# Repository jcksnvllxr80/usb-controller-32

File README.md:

# USB Controller 32

A USB HID gamepad controller built on the **PIC32MX250F128B** microcontroller. The firmware reads button inputs from GPIO pins, two potentiometers on the PIC32 ADC, and an **MCP23017** I2C I/O expander, then reports them to a host PC as a standard USB HID gamepad. The board-level serial path uses a **MAX3232** level shifter, and the MCU clock is provided by a **20 MHz crystal**. Built with **MPLAB Harmony 3**, **FreeRTOS**, and **C++**.

## Features

- USB HID gamepad with 18 button inputs (2 direct GPIO + 16 via MCP23017)
- 8-byte HID input report with 18 buttons, hat switch, and two live analog axes
- MCP23017 I2C I/O expander with interrupt-driven input detection
- MAX3232-backed debug serial / RS-232 path
- `POT_1` and `POT_2` sampled on `AN4` / `AN5` for `Z` and `Rz`
- Send-on-change HID reports for buttons and potentiometer axes
- Rate-limited serial logging for potentiometer changes with `POT_1` / `POT_2` identification
- FreeRTOS-based task scheduling
- UART debug logging and USB/HID diagnostics
- Green and red status LEDs

## Hardware Used

Main ICs and timing parts on this design:

- `PIC32MX250F128B` - main microcontroller, USB device controller, ADC, GPIO, I2C, and UART
- `MCP23017` - 16-bit I2C GPIO expander for the additional button inputs
- `MAX3232` - UART level shifter for the board's serial / RS-232 debug path
- `20 MHz crystal` - external clock source for the PIC32MX250F128B
- `2x linear potentiometers` - analog controls for `POT_1` and `POT_2`, mapped to HID `Z` and `Rz`
- `Mini USB breakout` - USB connector breakout for the device port, such as the small Adafruit mini USB breakout the board is using

## Architecture

### UML Class Diagram

### State Machine

## Pin Assignment Table

### PIC32MX250F128B Direct I/O

| Signal | Pin | Port | Direction | Description |
|---|---|---|---|---|
| MCLR | 1 | — | Input | Master clear (active-low reset); 10k pull-up to VDD; PICkit 5 pin 1 (VPP) |
| PGED1 | 2 | RA0 | Programming | ICSP data (PICkit 5 pin 4) |
| PGEC1 | 3 | RA1 | Programming | ICSP clock (PICkit 5 pin 5) |
| GREEN_LED | 4 | RB0 | Output | Green status LED |
| RED_LED | 5 | RB1 | Output | Red status LED |
| POT_1 | 6 | RB2 / AN4 | Input | Analog potentiometer mapped to HID Z axis |
| POT_2 | 7 | RB3 / AN5 | Input | Analog potentiometer mapped to HID Rz axis |
| VSS | 8 | — | Power | Ground |
| OSC1 | 9 | RA2 | Input | 20 MHz crystal input |
| OSC2 | 10 | RA3 | Output | 20 MHz crystal output |
| U1TX | 11 | RB4 | Output | UART1 transmit (debug) |
| U1RX | 12 | RA4 | Input | UART1 receive (debug) |
| VDD | 13 | — | Power | 5V supply |
| INTERRUPT_A | 14 | RB5 | Input | MCP23017 Port A interrupt (active-low) |
| VBUS | 15 | — | Power | USB 5V bus voltage; connected to VCC |
| INTERRUPT_B | 16 | RB7 | Input | MCP23017 Port B interrupt (active-low) |
| SCL1 | 17 | RB8 | Output | I2C1 clock to MCP23017 |
| SDA1 | 18 | RB9 | Bidirectional | I2C1 data to MCP23017 |
| VSS | 19 | — | Power | Ground |
| VCAP | 20 | — | Power | Internal core regulator output; 0.1µF cap to VSS |
| D+ | 21 | — | Bidirectional | USB data plus |
| D− | 22 | — | Bidirectional | USB data minus |
| VUSB3V3 | 23 | — | Power | USB 3.3V supply; decoupling capacitors to GND |
| RB13 | 24 | RB13 | NC | Not connected |
| BUTTON_1 | 25 | RB14 | Input | Direct button input 1 |
| BUTTON_2 | 26 | RB15 | Input | Direct button input 2 |
| AVSS | 27 | — | Power | Analog ground |
| AVDD | 28 | — | Power | 5V analog supply |

### MCP23017 I/O Expander (I2C address 0x20)

| Port | Pins | Direction | Pull-ups | Interrupt | Description |
|---|---|---|---|---|---|
| Port A | GPA0–GPA7 | Input | Enabled | Enabled (interrupt-on-change) | 8 button inputs |
| Port B | GPB0–GPB7 | Input | Enabled | Enabled (interrupt-on-change) | 8 button inputs |

### Input/Output Summary

| Type | Count | Source | Details |
|---|---|---|---|
| Button inputs (direct) | 2 | PIC32 GPIO | RB14, RB15 |
| Button inputs (expanded) | 16 | MCP23017 Port A & B | GPA0–7, GPB0–7 |
| Analog inputs | 2 | PIC32 ADC | POT_1 on AN4 drives HID Z, POT_2 on AN5 drives HID Rz |
| LED outputs | 2 | PIC32 GPIO | Green (RB0), Red (RB1) |
| USB HID | 1 | USB peripheral | 18 buttons, hat switch, X/Y centered, live Z/Rz in an 8-byte report |
| Debug UART | 1 | UART1 via MAX3232 | 115200 baud debug/serial path (TX: RB4, RX: RA4) |
| I2C bus | 1 | I2C1 | MCP23017 at 0x20 |

## Getting Started

### Prerequisites

- [MPLAB X IDE](https://www.microchip.com/mplab/mplab-x-ide) or the **MPLAB Extension for VS Code**
- [XC32 Compiler](https://www.microchip.com/xc32) (v4.x or later)
- [PIC32MX DFP](https://packs.download.microchip.com/) v1.6.369
- **PICkit 5** (or compatible Microchip programmer/debugger)
- Git

### Install MPLAB for VS Code

1. Open **VS Code** (or VS Code Insiders).
2. Go to the **Extensions** view (`Ctrl+Shift+X`).
3. Search for **"MPLAB"** and install the **Microchip MPLAB** extension pack.
4. The extension will prompt you to install the **XC32 compiler** and required device packs if they are not found. Follow the prompts.
5. Restart VS Code after installation.

### Clone and Build

```bash
git clone https://github.com/jcksnvllxr80/usb-controller-32.git
cd usb-controller-32
```

1. Open the folder in VS Code.
2. The MPLAB extension should detect the project automatically via the CMake configuration in the `cmake/` directory.
3. Select the **usb-controller-32** project and the **default** configuration from the MPLAB project view.
4. Click **Build** (or press `Ctrl+Shift+B`).

### Program the Device

1. Connect the **PICkit 5** to the ICSP header on your board (ensure correct pin 1 orientation).
2. In the MPLAB extension, select **PICkit 5** as the hardware tool.
3. Set the programming speed to **Low** if you encounter connection issues.
4. Click **Program** to flash the `.hex` file to the PIC32MX250F128B.

> Warning: Use a native **USB 2.0** port when connecting this controller to the PC. On some machines, USB 3.x ports/controllers can fail enumeration or produce a Windows Code 10 error with this hardware. If your machine does not have a USB 2.0 port, connect the controller through a **USB 2.0 hub**.

### Verify Operation

1. After programming, the device should enumerate as a USB HID gamepad on the host PC.
2. Open **Set up USB game controllers** (Windows) or a gamepad tester to confirm button presses and `Z` / `Rz` potentiometer movement are registered.
3. Connect a serial terminal (115200 baud, 8N1) to UART1 to view debug logs, potentiometer change logs, and issue commands.

## UART Diagnostics

Helper scripts:

- `powershell -ExecutionPolicy Bypass -File .\tools\uart_query.ps1`
- `powershell -ExecutionPolicy Bypass -File .\tools\uart_cmd.ps1 -cmd "status"`

Useful commands:

- `status` - GPIO, USB, and LED summary
- `usb` - USB device state and register dump
- `enum` - enumeration counters and last setup request
- `hid` - HID readiness, send counters, and current report bytes
- `usblog` - recent USB transaction log
- `usbdbg` - toggle live USB debug logging
- `usbreset` - soft detach/reattach to force re-enumeration

Automatic serial logs:

- Potentiometer changes are logged automatically as `[POT] POT_1 axis=...` and/or `[POT] POT_2 axis=...`
- Logs are only emitted when the scaled axis value changes
- Pot logs are rate-limited to 5 lines per second total

## Firmware Notes

- GPIO and MCP23017 interrupts only latch state. HID reports are built and sent from `APP_Tasks()`.
- `POT_1` and `POT_2` are polled in `APP_Tasks()`, scaled from 10-bit ADC samples to 8-bit HID axis values, and mapped to HID `Z` and `Rz`.
- Potentiometer state is cached, so a new HID report is only queued when a button changes or when the last-sent `Z` / `Rz` byte changes.
- Potentiometer serial logs identify which input changed (`POT_1`, `POT_2`, or both), skip repeated values, and are rate-limited to 5 lines per second.
- HID reports are only queued when button or axis state changes, which keeps traffic and debug noise down.

## Project Structure

```
usb-controller-32/
├── cmake/                      # CMake build configurations
├── docs/                       # Datasheets, block diagram, images
├── tools/                      # Flash and UART helper scripts
├── usb-controller-32/
│   ├── mcc/                    # MPLAB Code Configurator files
│   └── src/
│       ├── main.cpp            # Entry point (SYS_Initialize + SYS_Tasks)
│       ├── app.cpp / app.h     # App task, GPIO/MCP state, USB HID send path
│       ├── command_handler.cpp / .h # UART command parser and diagnostics
│       ├── gamepad.cpp / .h    # USB HID gamepad driver
│       ├── mcp23017.cpp / .h   # MCP23017 I2C I/O expander driver
│       ├── logger.cpp / .h     # UART debug logger (singleton)
│       ├── usb_debug.c / .h    # USB debug logging helpers
│       ├── config/             # Harmony-generated peripheral config
│       └── third_party/rtos/   # FreeRTOS source
└── README.md
```

## Sponsor

PCB prototyping for this project is sponsored by [PCBWay](https://www.pcbway.com/).

PCBWay makes it easy to go from design files to manufactured boards. Upload your Gerber files, pick your board specs (layers, thickness, surface finish, color, etc.), and get an instant quote. Orders typically ship within a few days. Their online ordering process is straightforward — just create an account, upload your files, review the specs, and check out.

## License

See Microchip's license terms in the source file headers.

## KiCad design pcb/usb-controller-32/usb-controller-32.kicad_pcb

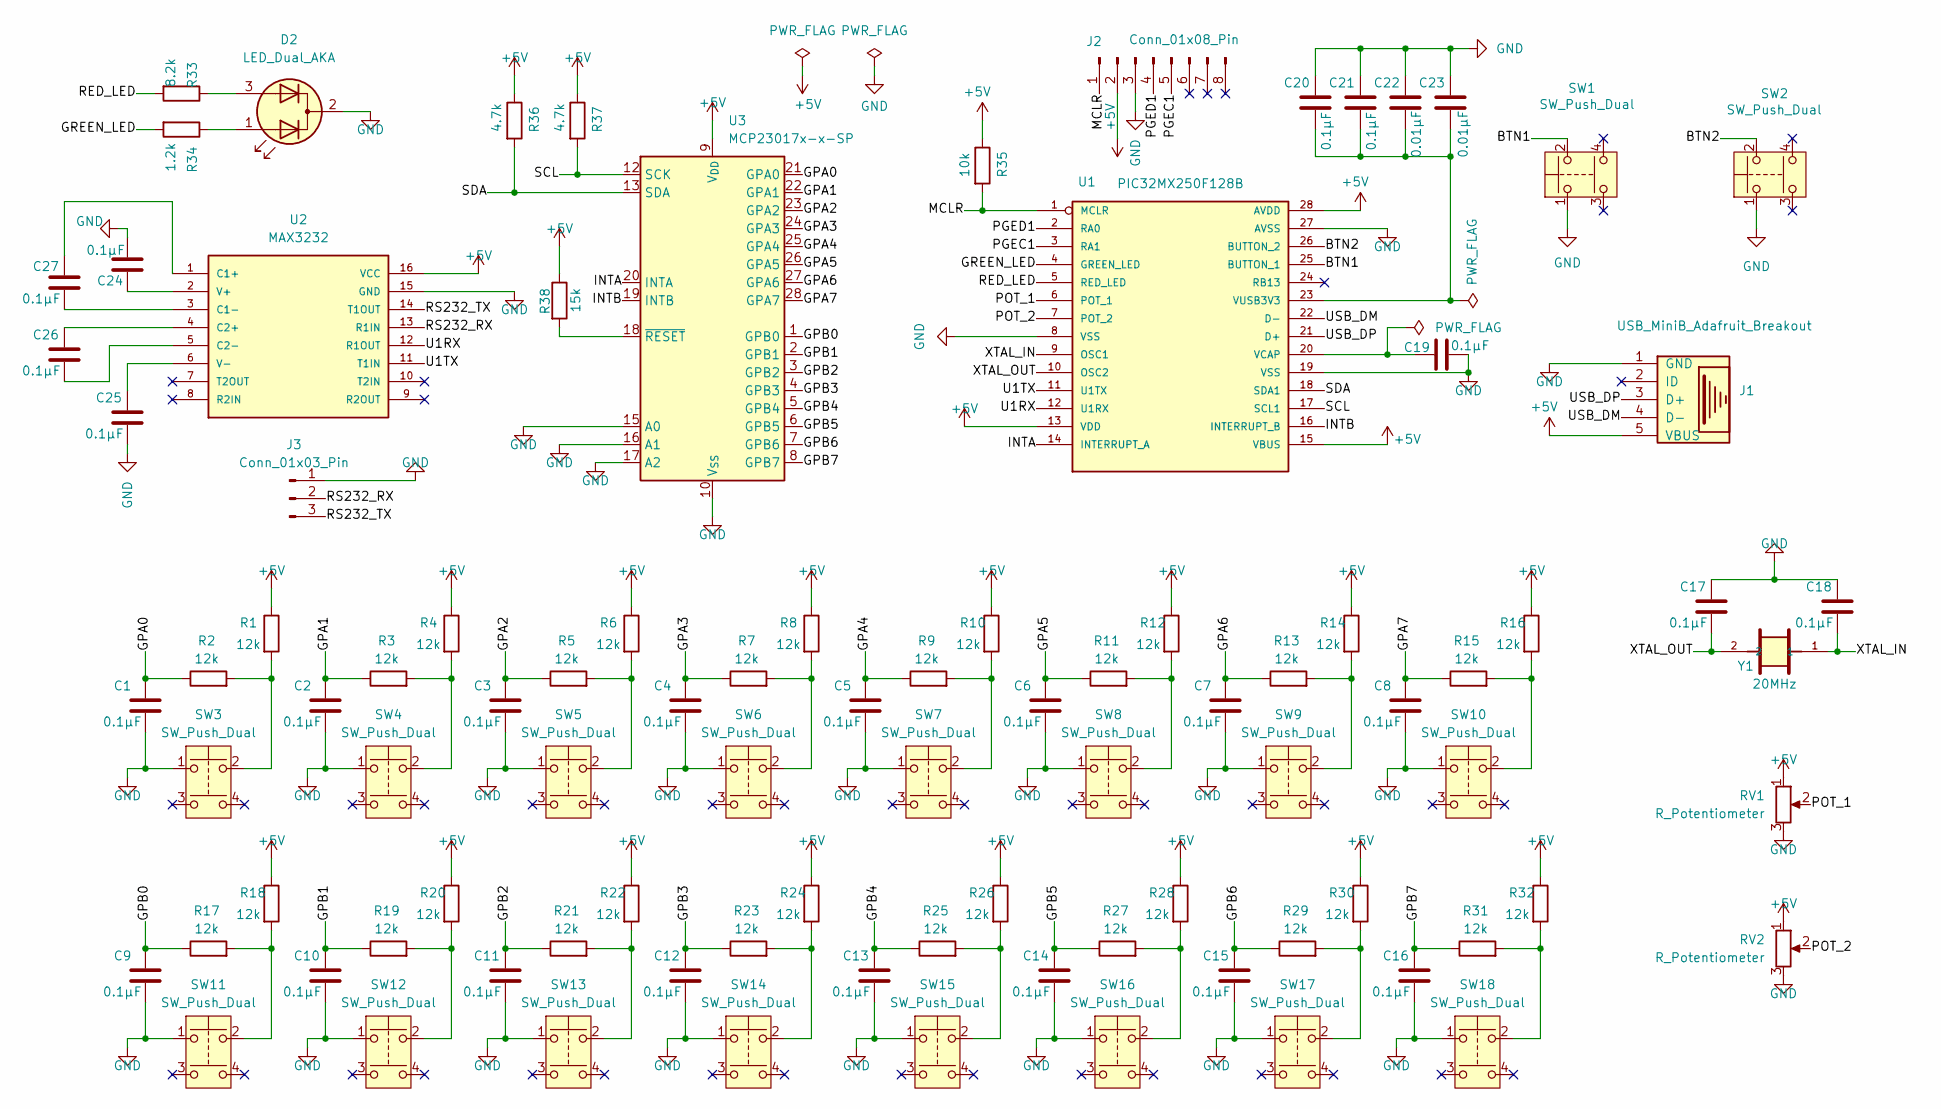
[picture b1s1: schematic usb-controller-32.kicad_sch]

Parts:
C1, C2, C3, C4, C5, C6, C7, C8, C9, C10, C11, C12, C13, C14, C15, C16, C17, C18, C19, C20, C21, C24, C25, C26, C27: 0.1µF; C_Disc_D5.0mm_W2.5mm_P2.50mm
C22, C23: 0.01µF; C_Disc_D5.0mm_W2.5mm_P2.50mm
D2: LED_Dual_AKA; LED_D3.0mm-3
J1: USB_MiniB_Adafruit_Breakout
J2: Conn_01x08_Pin; PinHeader_1x08_P2.54mm_Vertical
J3: Conn_01x03_Pin; PinHeader_1x03_P2.54mm_Vertical
R1, R2, R3, R4, R5, R6, R7, R8, R9, R10, R11, R12, R13, R14, R15, R16, R17, R18, R19, R20, R21, R22, R23, R24, R25, R26, R27, R28, R29, R30, R31, R32: 12k; R_Axial_DIN0207_L6.3mm_D2.5mm_P10.16mm_Horizontal
R33: 8.2k; R_Axial_DIN0207_L6.3mm_D2.5mm_P10.16mm_Horizontal
R34: 1.2k; R_Axial_DIN0207_L6.3mm_D2.5mm_P10.16mm_Horizontal
R35: 10k; R_Axial_DIN0207_L6.3mm_D2.5mm_P10.16mm_Horizontal
R36, R37: 4.7k; R_Axial_DIN0207_L6.3mm_D2.5mm_P10.16mm_Horizontal
R38: 15k; R_Axial_DIN0207_L6.3mm_D2.5mm_P10.16mm_Horizontal
RV1, RV2: R_Potentiometer; Potentiometer_Bourns_3386P_Vertical
SW1, SW2, SW3, SW4, SW5, SW6, SW7, SW8, SW9, SW10, SW11, SW12, SW13, SW14, SW15, SW16, SW17, SW18: SW_Push_Dual; SW_TH_Tactile_Omron_B3F-100x
U1: PIC32MX250F128B; DIP-28_W7.62mm
U2: MAX3232; DIP-16_W7.62mm
U3: MCP23017x-x-SP; DIP-28_W7.62mm
Y1: 20MHz; Crystal_HC49-4H_Vertical

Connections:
+5V: J1.5 (VBUS), J2.2, R1.1, R4.1, R6.1, R8.1, R10.1, R12.1, R14.1, R16.1, R18.1, R20.1, R22.1, R24.1, R26.1, R28.1, R30.1, R32.1, R35.1, R36.1, R37.1, R38.1, RV1.1, RV2.1, U1.13 (VDD), U1.15 (VBUS), U1.28 (AVDD), U2.16 (VCC), U3.9 (V_{DD})
/BTN1: SW1.2, U1.25 (BUTTON_1)
/BTN2: SW2.2, U1.26 (BUTTON_2)
/GPA0: C1.2, R2.1, U3.21 (GPA0)
/GPA1: C2.2, R3.1, U3.22 (GPA1)
/GPA2: C3.2, R5.1, U3.23 (GPA2)
/GPA3: C4.2, R7.1, U3.24 (GPA3)
/GPA4: C5.2, R9.1, U3.25 (GPA4)
/GPA5: C6.2, R11.1, U3.26 (GPA5)
/GPA6: C7.2, R13.1, U3.27 (GPA6)
/GPA7: C8.2, R15.1, U3.28 (GPA7)
/GPB0: C9.2, R17.1, U3.1 (GPB0)
/GPB1: C10.2, R19.1, U3.2 (GPB1)
/GPB2: C11.2, R21.1, U3.3 (GPB2)
/GPB3: C12.2, R23.1, U3.4 (GPB3)
/GPB4: C13.2, R25.1, U3.5 (GPB4)
/GPB5: C14.2, R27.1, U3.6 (GPB5)
/GPB6: C15.2, R29.1, U3.7 (GPB6)
/GPB7: C16.2, R31.1, U3.8 (GPB7)
/GREEN_LED: R34.2, U1.4 (GREEN_LED)
/INTA: U1.14 (INTERRUPT_A), U3.20 (INTA)
/INTB: U1.16 (INTERRUPT_B), U3.19 (INTB)
/MCLR: J2.1, R35.2, U1.1 (MCLR)
/PGEC1: J2.5, U1.3 (RA1)
/PGED1: J2.4, U1.2 (RA0)
/POT_1: RV1.2, U1.6 (POT_1)
/POT_2: RV2.2, U1.7 (POT_2)
/RED_LED: R33.2, U1.5 (RED_LED)
/RS232_RX: J3.2, U2.13 (R1IN)
/RS232_TX: J3.3, U2.14 (T1OUT)
/SCL: R37.2, U1.17 (SCL1), U3.12 (SCK)
/SDA: R36.2, U1.18 (SDA1), U3.13 (SDA)
/U1RX: U1.12 (U1RX), U2.12 (R1OUT)
/U1TX: U1.11 (U1TX), U2.11 (T1IN)
/USB_DM: J1.4 (D-), U1.22 (D-)
/USB_DP: J1.3 (D+), U1.21 (D+)
/XTAL_IN: C18.1, U1.9 (OSC1), Y1.1
/XTAL_OUT: C17.1, U1.10 (OSC2), Y1.2
GND: C1.1, C2.1, C3.1, C4.1, C5.1, C6.1, C7.1, C8.1, C9.1, C10.1, C11.1, C12.1, C13.1, C14.1, C15.1, C16.1, C17.2, C18.2, C19.1, C20.2, C21.2, C22.2, C23.2, C24.1, C25.1, D2.2 (K), J1.1 (GND), J2.3, J3.1, RV1.3, RV2.3, SW1.1, SW2.1, SW3.1, SW4.1, SW5.1, SW6.1, SW7.1, SW8.1, SW9.1, SW10.1, SW11.1, SW12.1, SW13.1, SW14.1, SW15.1, SW16.1, SW17.1, SW18.1, U1.8 (VSS), U1.19 (VSS), U1.27 (AVSS), U2.15 (GND), U3.10 (V_{SS}), U3.15 (A0), U3.16 (A1), U3.17 (A2)
unnamed: D2.1 (A1), R34.1
unnamed: D2.3 (A2), R33.1
unnamed: R1.2, R2.2, SW3.2
unnamed: R3.2, R4.2, SW4.2
unnamed: R5.2, R6.2, SW5.2
unnamed: R7.2, R8.2, SW6.2
unnamed: R9.2, R10.2, SW7.2
unnamed: R11.2, R12.2, SW8.2
unnamed: R13.2, R14.2, SW9.2
unnamed: R15.2, R16.2, SW10.2
unnamed: R17.2, R18.2, SW11.2
unnamed: R19.2, R20.2, SW12.2
unnamed: R21.2, R22.2, SW13.2
unnamed: R23.2, R24.2, SW14.2
unnamed: R25.2, R26.2, SW15.2
unnamed: R27.2, R28.2, SW16.2
unnamed: R29.2, R30.2, SW17.2
unnamed: R31.2, R32.2, SW18.2
unnamed: C19.2, U1.20 (VCAP)
unnamed: C20.1, C21.1, C22.1, C23.1, U1.23 (VUSB3V3)
unnamed: C27.2, U2.1 (C1+)
unnamed: C27.1, U2.3 (C1-)
unnamed: C26.2, U2.4 (C2+)
unnamed: C26.1, U2.5 (C2-)
unnamed: C24.2, U2.2 (V+)
unnamed: C25.2, U2.6 (V-)
unnamed: R38.2, U3.18 (~RESET)

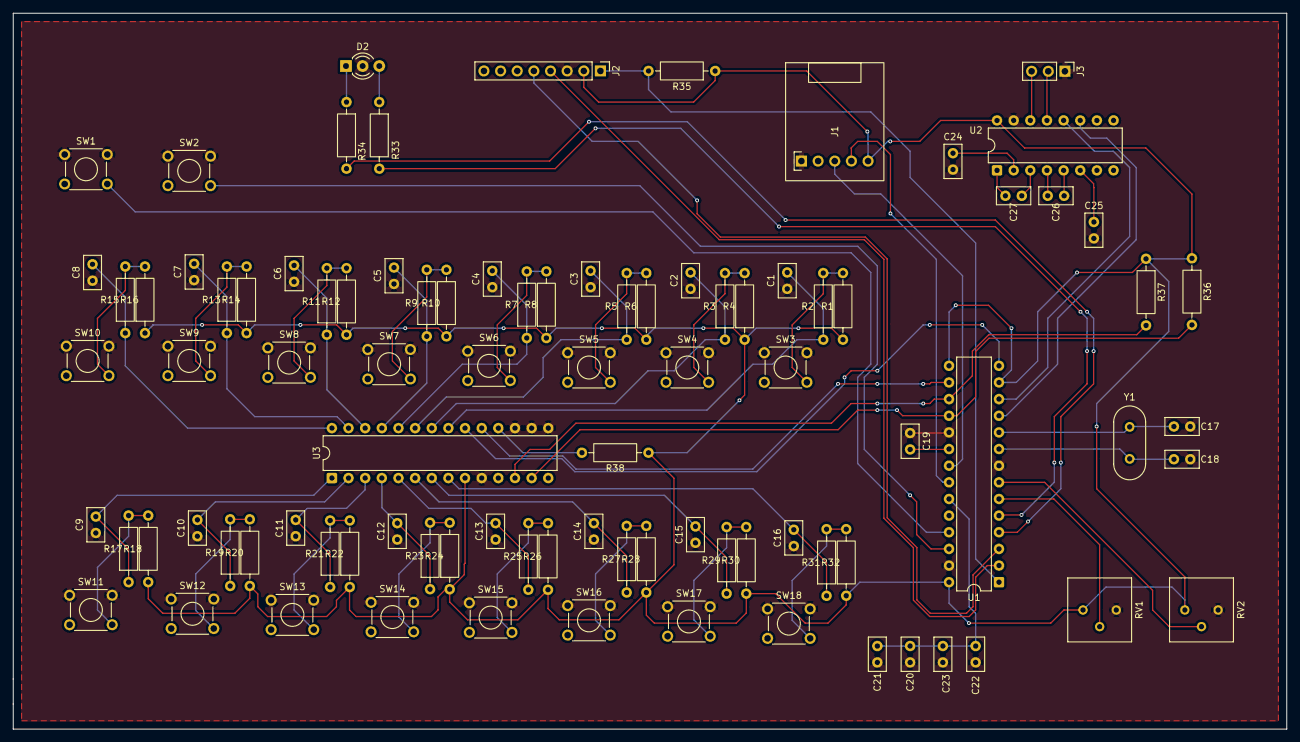
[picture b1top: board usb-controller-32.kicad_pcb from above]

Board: 2 copper layers, 194.3 x 109.2 mm, 93 parts (0 on the bottom side), 66 nets.

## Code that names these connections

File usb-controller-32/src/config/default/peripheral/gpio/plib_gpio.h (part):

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// *****************************************************************************


/*** Macros for GREEN_LED pin ***/
#define GREEN_LED_Set()               (LATBSET = (1<<0))
#define GREEN_LED_Clear()             (LATBCLR = (1<<0))
#define GREEN_LED_Toggle()            (LATBINV= (1<<0))
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#define GREEN_LED_InputEnable()       (TRISBSET = (1<<0))
#define GREEN_LED_Get()               ((PORTB >> 0) & 0x1)
#define GREEN_LED_GetLatch()          ((LATB >> 0) & 0x1)
#define GREEN_LED_PIN                  GPIO_PIN_RB0

/*** Macros for RED_LED pin ***/
#define RED_LED_Set()               (LATBSET = (1<<1))
#define RED_LED_Clear()             (LATBCLR = (1<<1))
#define RED_LED_Toggle()            (LATBINV= (1<<1))
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#define RED_LED_InputEnable()       (TRISBSET = (1<<1))
#define RED_LED_Get()               ((PORTB >> 1) & 0x1)
#define RED_LED_GetLatch()          ((LATB >> 1) & 0x1)
#define RED_LED_PIN                  GPIO_PIN_RB1

/*** Macros for POT_1 pin ***/
#define POT_1_Get()               ((PORTB >> 2) & 0x1)
#define POT_1_GetLatch()          ((LATB >> 2) & 0x1)
#define POT_1_PIN                  GPIO_PIN_RB2

/*** Macros for POT_2 pin ***/
#define POT_2_Get()               ((PORTB >> 3) & 0x1)
#define POT_2_GetLatch()          ((LATB >> 3) & 0x1)
#define POT_2_PIN                  GPIO_PIN_RB3

/*** Macros for INTERRUPT_A pin ***/
#define INTERRUPT_A_Set()               (LATBSET = (1<<5))
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
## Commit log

2026-03-17 Add configuration settings and update component positions in YAML files
2026-03-17 Add FreeRTOS include directories and update heap size configuration
2026-03-17 Update GPIO macros and add BUTTON_1, BUTTON_2, INTERRUPT_A, and INTERRUPT_B definitions
2026-03-17 Implement gamepad functionality with MCP23017 support and logging capabilities
2026-03-17 add docs and images
2026-03-17 add more docs and and put on README
2026-03-17 remove default profile
2026-03-17 Add CHANGE_NOTICE interrupt handling and GPIO callback support
2026-03-17 Implement GPIO interrupt handling and update button state management
2026-03-17 Fix button press detection logic and add logging for button state changes and MCP23017 interrupts
2026-03-22 move clock source from frc to primary osc
2026-03-22 change the i2c brg to 400khz from 50khz
2026-03-22 change chip package in mcc
2026-03-22 remove everything except uart and buttons
2026-03-22 Refactor button handling logic to use interrupt callbacks and improve state tracking
2026-03-22 Add pull-up resistors for PORTB and update button logging
2026-03-22 Fix UART write handling in Logger to ensure txDone_ is set correctly on failure
2026-03-22 add i2c1
2026-03-22 mcp23017 works properly
2026-04-06 add max3232cpe datasheet
2026-04-06 Update USB Controller configuration and image
    - Updated the mcc-config.mc4 file to include the i2c1 module in the USB controller configuration.
    - Modified the bd-usb-controller-32.png image file.
2026-04-07 get the buttons working
2026-04-07 WIP start over (#1)
    * remove everything except uart and buttons
    * Refactor button handling logic to use interrupt callbacks and improve state tracking
    * Add pull-up resistors for PORTB and update button logging
    * Fix UART write handling in Logger to ensure txDone_ is set correctly on failure
    * add i2c1
    * mcp23017 works properly
2026-04-07 update readme to reflect new changes
2026-04-07 Implement USB attach delay and improve USB detachment handling
2026-04-07 Refactor USB device initialization and improve HID handling
2026-04-07 Add GPIO macros for POT_1 and POT_2 pins and update core configuration
2026-04-07 feat: Update block diagram and add potentiometer support to USB controller
    - Changed background colors in the block diagram for better visibility.
    - Added new elements to the block diagram, including analog inputs and potentiometers.
    - Updated the USB controller application to include potentiometer reading and logging.
    - Introduced a new GamepadReport structure to handle gamepad data more effectively.
    - Implemented ADC initialization and reading functions for potentiometers.
    - Enhanced command handler to log potentiometer values.
2026-04-07 modify block diagram
2026-04-07 fix: update MCP23017 bank LEDs to reflect any active input
2026-04-08 fix microcontroller pin table in readme
2026-04-08 add pcb project
2026-04-10 add mini b usb module footprint and sch
2026-04-10 add adafruit usb mini-b model and footprint
2026-04-10 update adafruit breakout footprint and model
2026-04-12 - finish schematic - add BOM
2026-04-12 add all footprints to PCB
2026-04-12 add claude generated python script to layout pcb add resulting pcb of aformentioned script run
2026-04-12 use different crystal footprint
2026-04-12 update pcb replace led footprint with gnd in middle
2026-04-12 add routed pcb
2026-04-13 resolve DRC errors and create fabouts
2026-04-13 Feature/pcb (#2)
    * add pcb project
    * add mini b usb module footprint and sch
    * add adafruit usb mini-b model and footprint
    * update adafruit breakout footprint and model
    * - finish schematic
    - add BOM
2026-04-13 add pcbway shoutout
2026-04-13 change via size to 0.2mm drill hole with 0.4mm diameter
2026-04-13 change via size to 0.2mm drill hole with 0.4mm diameter (#3)

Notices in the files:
usb-controller-32/src/config/default/peripheral/gpio/plib_gpio.h:
Copyright (C) 2019 Microchip Technology Inc. and its subsidiaries.
